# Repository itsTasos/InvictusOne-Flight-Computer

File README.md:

# InvictusOne Flight Computer

A 4-layer flight-data acquisition and logging board for high-power model rockets. The design combines a 3S LiPo power front end, an STM32G474 microcontroller, multiple flight sensors, non-volatile storage, CAN-FD and UART interfaces, and an external watchdog.

The board is intended to measure, timestamp, store, and communicate flight data. It does not include ignition, pyrotechnic, or recovery-deployment circuitry.

## Features

- STM32G474RET6 main controller with 8 MHz high-speed and 32.768 kHz low-speed crystals.
- BMI088 accelerometer and gyroscope, plus an ADXL375 high-g accelerometer with a measurement range up to ±200 g.
- LPS22DF absolute pressure sensor for pressure-based altitude estimation in application firmware.
- 128-Mbit (16-MiB) W25Q128 serial NOR flash for flight-data storage.
- CAN-FD transceiver with line protection and selectable 120 Ω termination.
- 3S battery input protection, electronic fuse, battery-current monitoring, and 3.3 V buck conversion.
- External watchdog connected to the MCU reset line.
- 29 test points on the bottom side.

## Specifications

| Item | Design specification |
|---|---|
| Battery input | 3S LiPo, 9.0–12.6 V nominal operating range |
| Battery protection | TPS25940 eFuse; nominal undervoltage rising/falling thresholds of about 8.67 V / 8.14 V, overvoltage cutoff about 13.53 V |
| Input current limit | About 1.74 A, set by the eFuse current-limit resistor |
| Main logic rail | 3.3 V from a TPS62902 synchronous buck converter |
| Sensor rails | 3V3_SENS and 3V3_BARO are ferrite-filtered branches of 3.3 V, not separate regulated outputs |
| Data storage | 128 Mbit / 16 MiB serial NOR flash |
| Communication | CAN-FD, 3.3 V UART, SWD |
| PCB outline | 50 × 80 mm |
| PCB construction | 4 copper layers, nominal 1.6 mm thickness |
| Mounting | Four 3.2 mm non-plated holes on a 40 × 70 mm pattern |
| Test access | 29 bottom-side test points |

Power thresholds and current limit are nominal resistor-based calculations. They are not per-cell LiPo protection thresholds or measured performance limits.

## Main components

| Reference | Part | Function |
|---|---|---|
| U1 | STM32G474RET6 | Main microcontroller; sensor acquisition, logging control, and communications |
| U2 | TPS3431SQDRBRQ1 | External watchdog; its output can reset the MCU |
| U3 | BMI088 | Accelerometer and gyroscope |
| U4 | ADXL375BCCZ | High-g accelerometer, ±200 g range |
| U5 | LPS22DFTR | Absolute pressure sensor |
| U6 | W25Q128JVSIQ | 128-Mbit serial NOR flash |
| U7 | TCAN3413DR | CAN-FD physical-layer transceiver |
| U8 | TPS25940AQRVCRQ1 | Input eFuse, voltage monitoring, current limiting, and current monitor |
| U9 | TPS62902QRYTRQ1 | Battery-to-3.3 V buck converter |
| U10 | PESD2CANFD24VT-Q | CAN bus transient protection |
| D2 | SMAJ13A-TR | Battery-input TVS diode |
| L1 | XGL4020-102ME, 1 µH | Buck-converter power inductor |

## Power and signal architecture

Battery power enters J1 as VBAT_RAW. The input TVS and eFuse feed VBAT_PROTECTED, which supplies the 3.3 V buck converter and is also available at J2 pin 1. The buck output is 3V3_MAIN. Ferrite filters create the 3V3_SENS branch for the inertial sensors, the 3V3_BARO branch for the pressure sensor, and a filtered VDDA branch for the MCU ADC.

The BMI088 uses SPI1, the ADXL375 uses SPI2, the pressure sensor uses I2C3, and the external flash uses SPI3. The MCU connects to the CAN-FD transceiver through FDCAN1, to J3 through USART2, and to a debug probe through SWD at J4. All board domains share a common ground; the sensor supply branches are filtered but not galvanically isolated.

See [Hardware design](docs/hardware-design.md) for the power path and design calculations, [Connector pinout](docs/pinout.md) for connector and test-point details, and [Programming and debug](docs/programming.md) for the custom SWD connection.

## External connectors

| Connector | Pin | Signal |
|---|---:|---|
| J1 — battery | 1 | VBAT_RAW, battery positive |
|  | 2 | GND |
| J2 — CAN module bus | 1 | VBAT_PROTECTED, battery voltage |
|  | 2 | GND |
|  | 3 | CAN_H |
|  | 4 | CAN_L |
| J3 — UART | 1 | 3V3_MAIN |
|  | 2 | GND |
|  | 3 | UART_TX from MCU |
|  | 4 | UART_RX to MCU |
| J4 — SWD | 1 | 3V3_MAIN / target reference |
|  | 2 | SWDIO |
|  | 3 | GND |
|  | 4 | SWCLK |
|  | 5 | GND |
|  | 6 | NRST |

**J2 pin 1 carries protected battery voltage, not 3.3 V.** J3 is a 3.3 V UART interface, not RS-232. J4 uses a custom six-contact assignment and is not the standard TC2030-CTX pinout. Confirm the pin numbering and cable wiring before connecting external equipment.

## Mechanical orientation

The board is 50 × 80 mm. The +X nose direction is marked on the silkscreen along the long board axis. The pressure-sensor port should remain unobstructed when installed. The four mounting holes are non-plated and form a 40 × 70 mm rectangle.

## Repository layout

- hardware/kicad/ — KiCad project, PCB, hierarchical schematic, design rules, and local symbol and footprint libraries.
- docs/schematic.pdf — rendered hierarchical schematic.
- docs/assets/board-overview.png — PCB layout illustration.
- docs/ — hardware overview, connector pinout, and programming guide.

## Opening the design

Open hardware/kicad/HPR_FC_G474_3S.kicad_pro in KiCad. The PCB, hierarchical schematic, local libraries, and design-rule file are kept together under hardware/kicad/; the project uses paths relative to that directory.

## Design boundaries

The board has no battery charger, cell balancer, individual-cell monitor, or guaranteed reverse-polarity protection. The eFuse monitors the pack input as a whole. Its nominal undervoltage threshold is below the safe minimum for some individual 3S LiPo cells, so it must not be used as cell-level protection.

The CAN interface is not galvanically isolated. The input TVS clamp can exceed the eFuse absolute-maximum input voltage under some surge conditions; validate the power source, wiring, and transient environment for the intended installation. This board is a sensing, logging, and communications platform, not a deployment controller.

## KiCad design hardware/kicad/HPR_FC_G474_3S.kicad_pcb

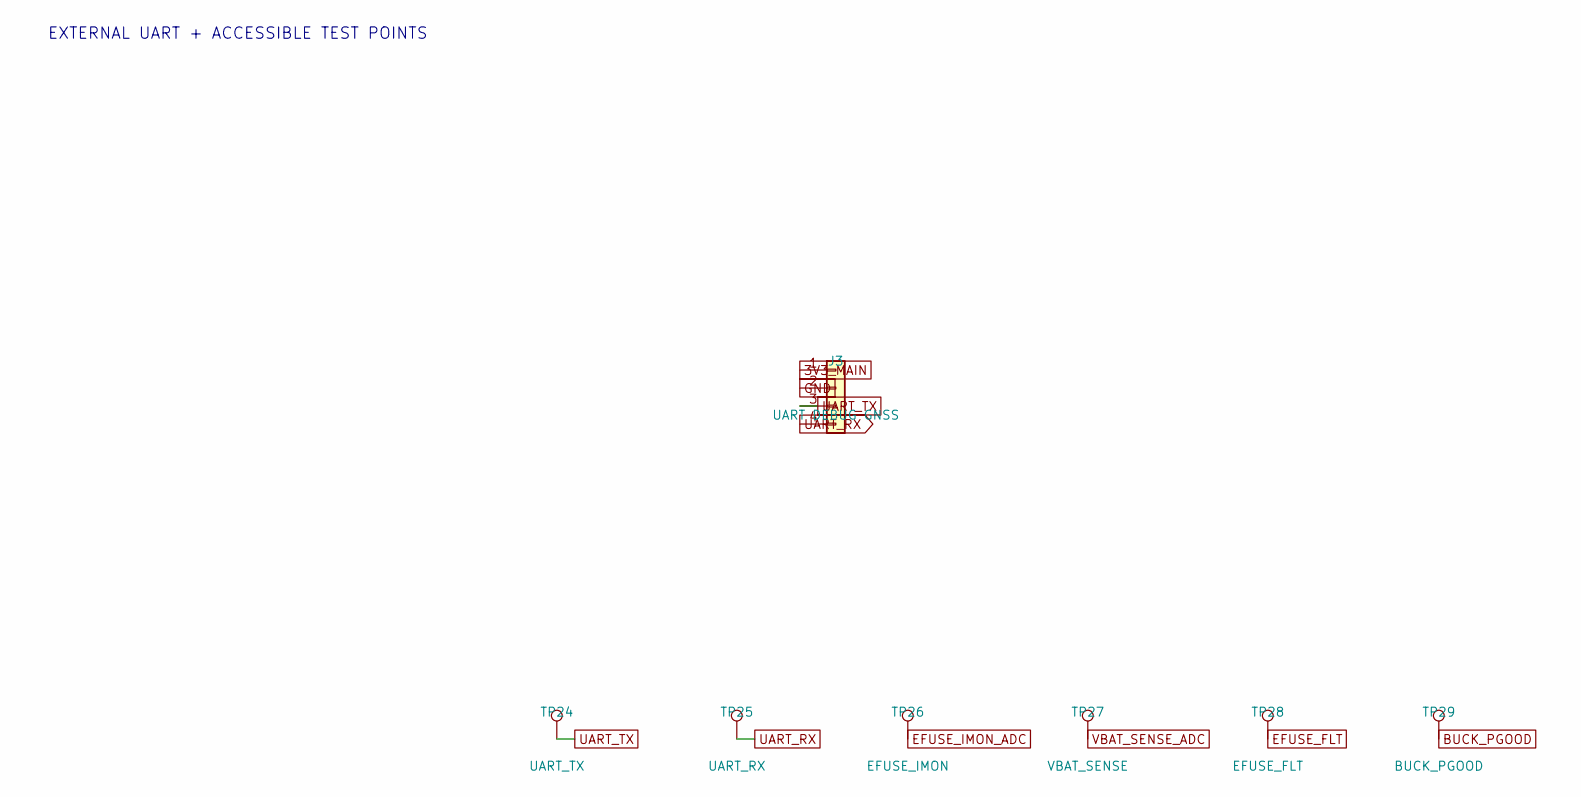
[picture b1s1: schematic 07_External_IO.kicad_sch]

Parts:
J3: UART DEBUG GNSS; JST_GH_SM04B-GHS-TB_1x04-1MP_P1.25mm_Horizontal
TP24: UART_TX; TestPoint_Pad_D1.0mm
TP25: UART_RX; TestPoint_Pad_D1.0mm
TP26: EFUSE_IMON; TestPoint_Pad_D1.0mm
TP27: VBAT_SENSE; TestPoint_Pad_D1.0mm
TP28: EFUSE_FLT; TestPoint_Pad_D1.0mm
TP29: BUCK_PGOOD; TestPoint_Pad_D1.0mm

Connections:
3V3_MAIN: J3.1; also elsewhere on the board
BUCK_PGOOD: TP29.1 (1_1); also elsewhere on the board
EFUSE_FLT: TP28.1 (1_1); also elsewhere on the board
EFUSE_IMON_ADC: TP26.1 (1_1); also elsewhere on the board
GND: J3.2; also elsewhere on the board
UART_RX: J3.4, TP25.1 (1_1); also elsewhere on the board
UART_TX: J3.3, TP24.1 (1_1); also elsewhere on the board
VBAT_SENSE_ADC: TP27.1 (1_1); also elsewhere on the board

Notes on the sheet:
EXTERNAL UART + ACCESSIBLE TEST POINTS

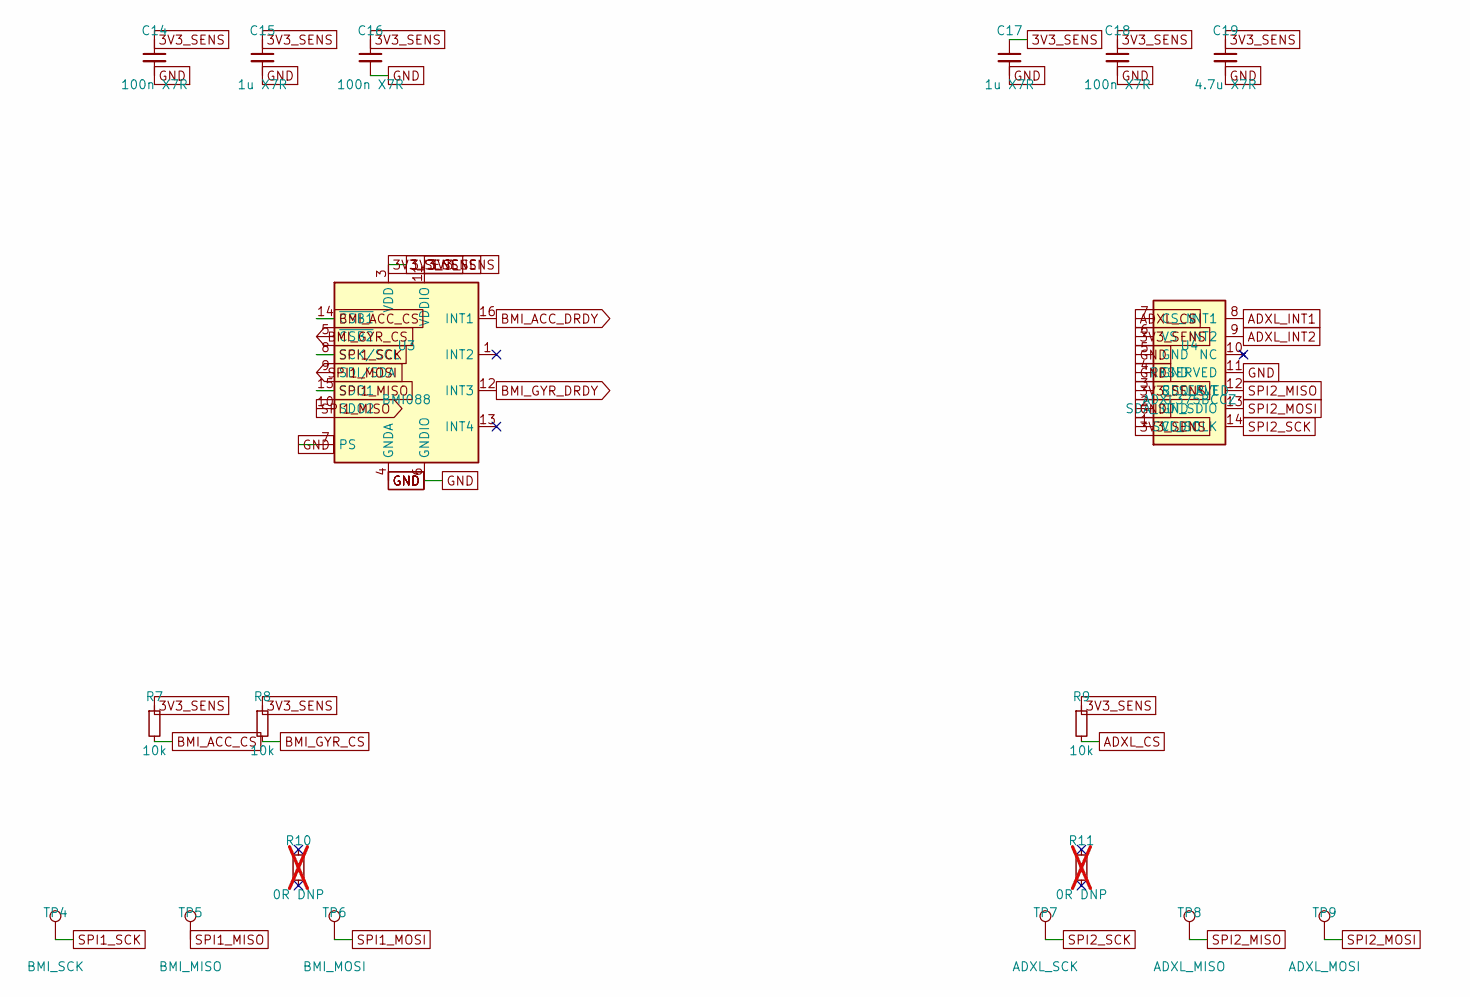
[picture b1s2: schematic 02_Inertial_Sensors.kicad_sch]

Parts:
C14, C16, C18: 100n X7R; C_0402_1005Metric
C15, C17: 1u X7R; C_0603_1608Metric
C19: 4.7u X7R; C_0603_1608Metric
R7, R8, R9: 10k; R_0402_1005Metric
R10, R11: 0R DNP; R_0402_1005Metric; not fitted
TP4: BMI_SCK; TestPoint_Pad_D1.0mm
TP5: BMI_MISO; TestPoint_Pad_D1.0mm
TP6: BMI_MOSI; TestPoint_Pad_D1.0mm
TP7: ADXL_SCK; TestPoint_Pad_D1.0mm
TP8: ADXL_MISO; TestPoint_Pad_D1.0mm
TP9: ADXL_MOSI; TestPoint_Pad_D1.0mm
U3: BMI088; Bosch_LGA-16_4.5x3mm_P0.5mm_LayoutBorder7x1y_ClockwisePinNu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; MPN BMI088
U4: ADXL375BCCZ; Analog_ADXL375_CC-14-1_LGA14_3x5mm_P0.8mm; MPN ADXL375BCCZ

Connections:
3V3_SENS: C14.1, C15.1, C16.1, C17.1, C18.1, C19.1, R7.1, R8.1, R9.1, U3.3 (VDD), U3.11 (VDDIO), U4.1 (VDDIO), U4.3 (RESERVED), U4.6 (VS); also elsewhere on the board
ADXL_CS: R9.2, U4.7 (CS_N); also elsewhere on the board
ADXL_INT1: U4.8 (INT1); also elsewhere on the board
ADXL_INT2: U4.9 (INT2); also elsewhere on the board
BMI_ACC_CS: R7.2, U3.14 (~CSB1); also elsewhere on the board
BMI_ACC_DRDY: U3.16 (INT1); also elsewhere on the board
BMI_GYR_CS: R8.2, U3.5 (~CSB2); also elsewhere on the board
BMI_GYR_DRDY: U3.12 (INT3); also elsewhere on the board
GND: C14.2, C15.2, C16.2, C17.2, C18.2, C19.2, U3.2 (GNDA), U3.4 (GNDA), U3.6 (GNDIO), U3.7 (PS), U4.2 (GND), U4.4 (GND), U4.5 (GND), U4.11 (RESERVED); also elsewhere on the board
SPI1_MISO: TP5.1 (1_1), U3.10 (SDO2), U3.15 (SDO1); also elsewhere on the board
SPI1_MOSI: TP6.1 (1_1), U3.9 (SDI/SDA); also elsewhere on the board
SPI1_SCK: TP4.1 (1_1), U3.8 (SCK/SCL); also elsewhere on the board
SPI2_MISO: TP8.1 (1_1), U4.12 (SDO_ALT); also elsewhere on the board
SPI2_MOSI: TP9.1 (1_1), U4.13 (SDA_SDI_SDIO); also elsewhere on the board
SPI2_SCK: TP7.1 (1_1), U4.14 (SCL_SCLK); also elsewhere on the board

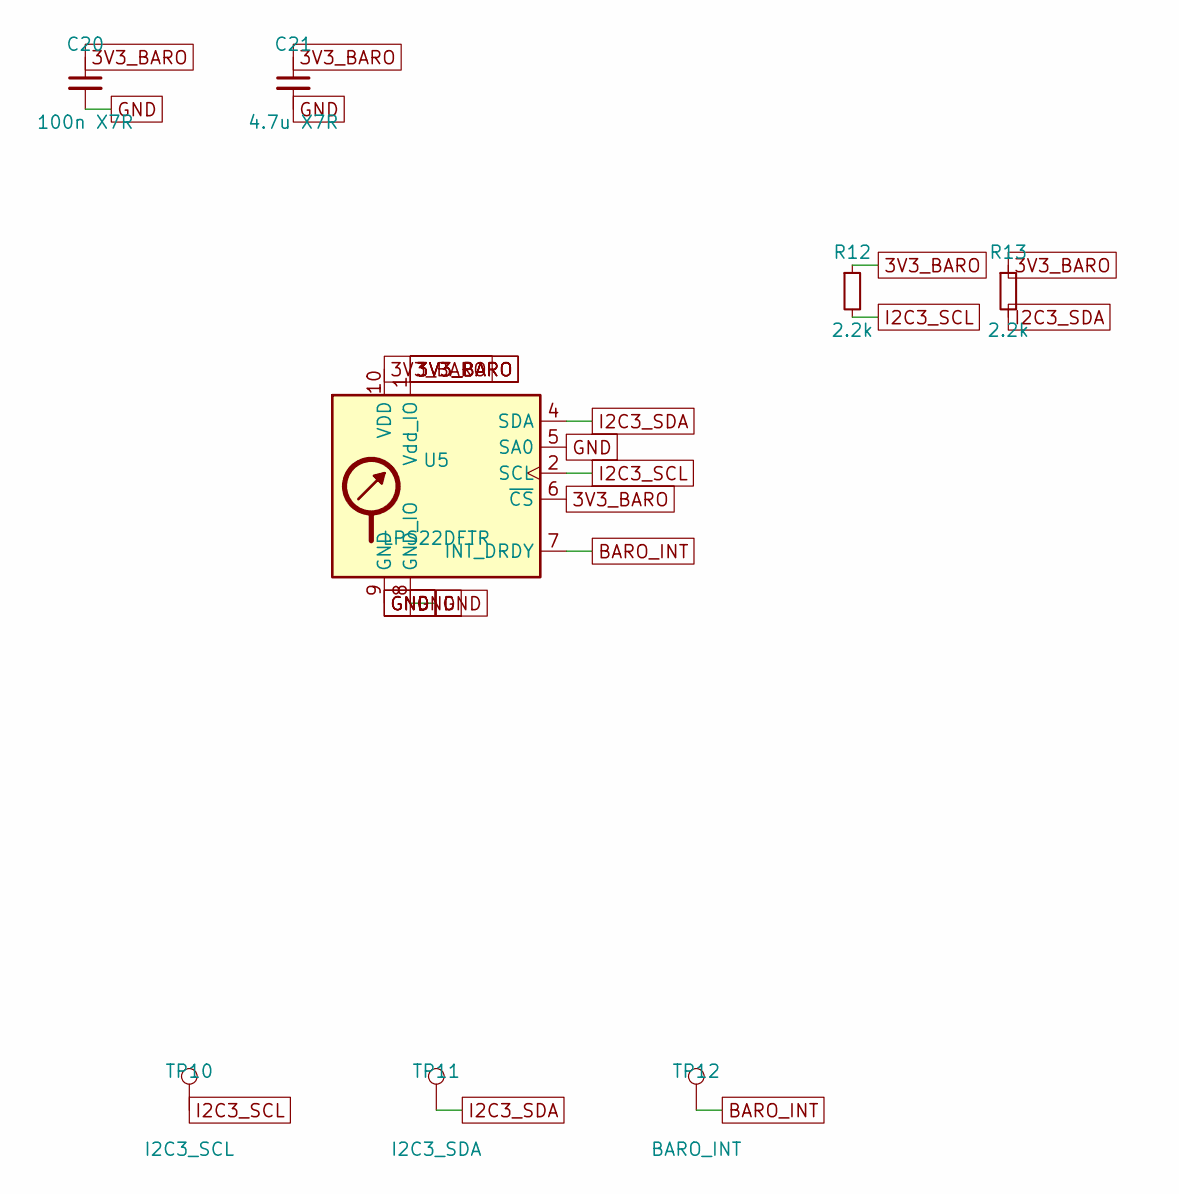
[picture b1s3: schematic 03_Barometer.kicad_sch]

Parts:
C20: 100n X7R; C_0402_1005Metric
C21: 4.7u X7R; C_0603_1608Metric
R12, R13: 2.2k; R_0402_1005Metric
TP10: I2C3_SCL; TestPoint_Pad_D1.0mm
TP11: I2C3_SDA; TestPoint_Pad_D1.0mm
TP12: BARO_INT; TestPoint_Pad_D1.0mm
U5: LPS22DFTR; ST_HLGA-10_2x2mm_P0.5mm_LayoutBorder3x2y; MPN LPS22DFTR

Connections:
3V3_BARO: C20.1, C21.1, R12.1, R13.1, U5.1 (Vdd_IO), U5.6 (~CS), U5.10 (VDD); also elsewhere on the board
BARO_INT: TP12.1 (1_1), U5.7 (INT_DRDY); also elsewhere on the board
GND: C20.2, C21.2, U5.3 (GND), U5.5 (SA0), U5.8 (GND_IO), U5.9 (GND); also elsewhere on the board
I2C3_SCL: R12.2, TP10.1 (1_1), U5.2 (SCL); also elsewhere on the board
I2C3_SDA: R13.2, TP11.1 (1_1), U5.4 (SDA); also elsewhere on the board

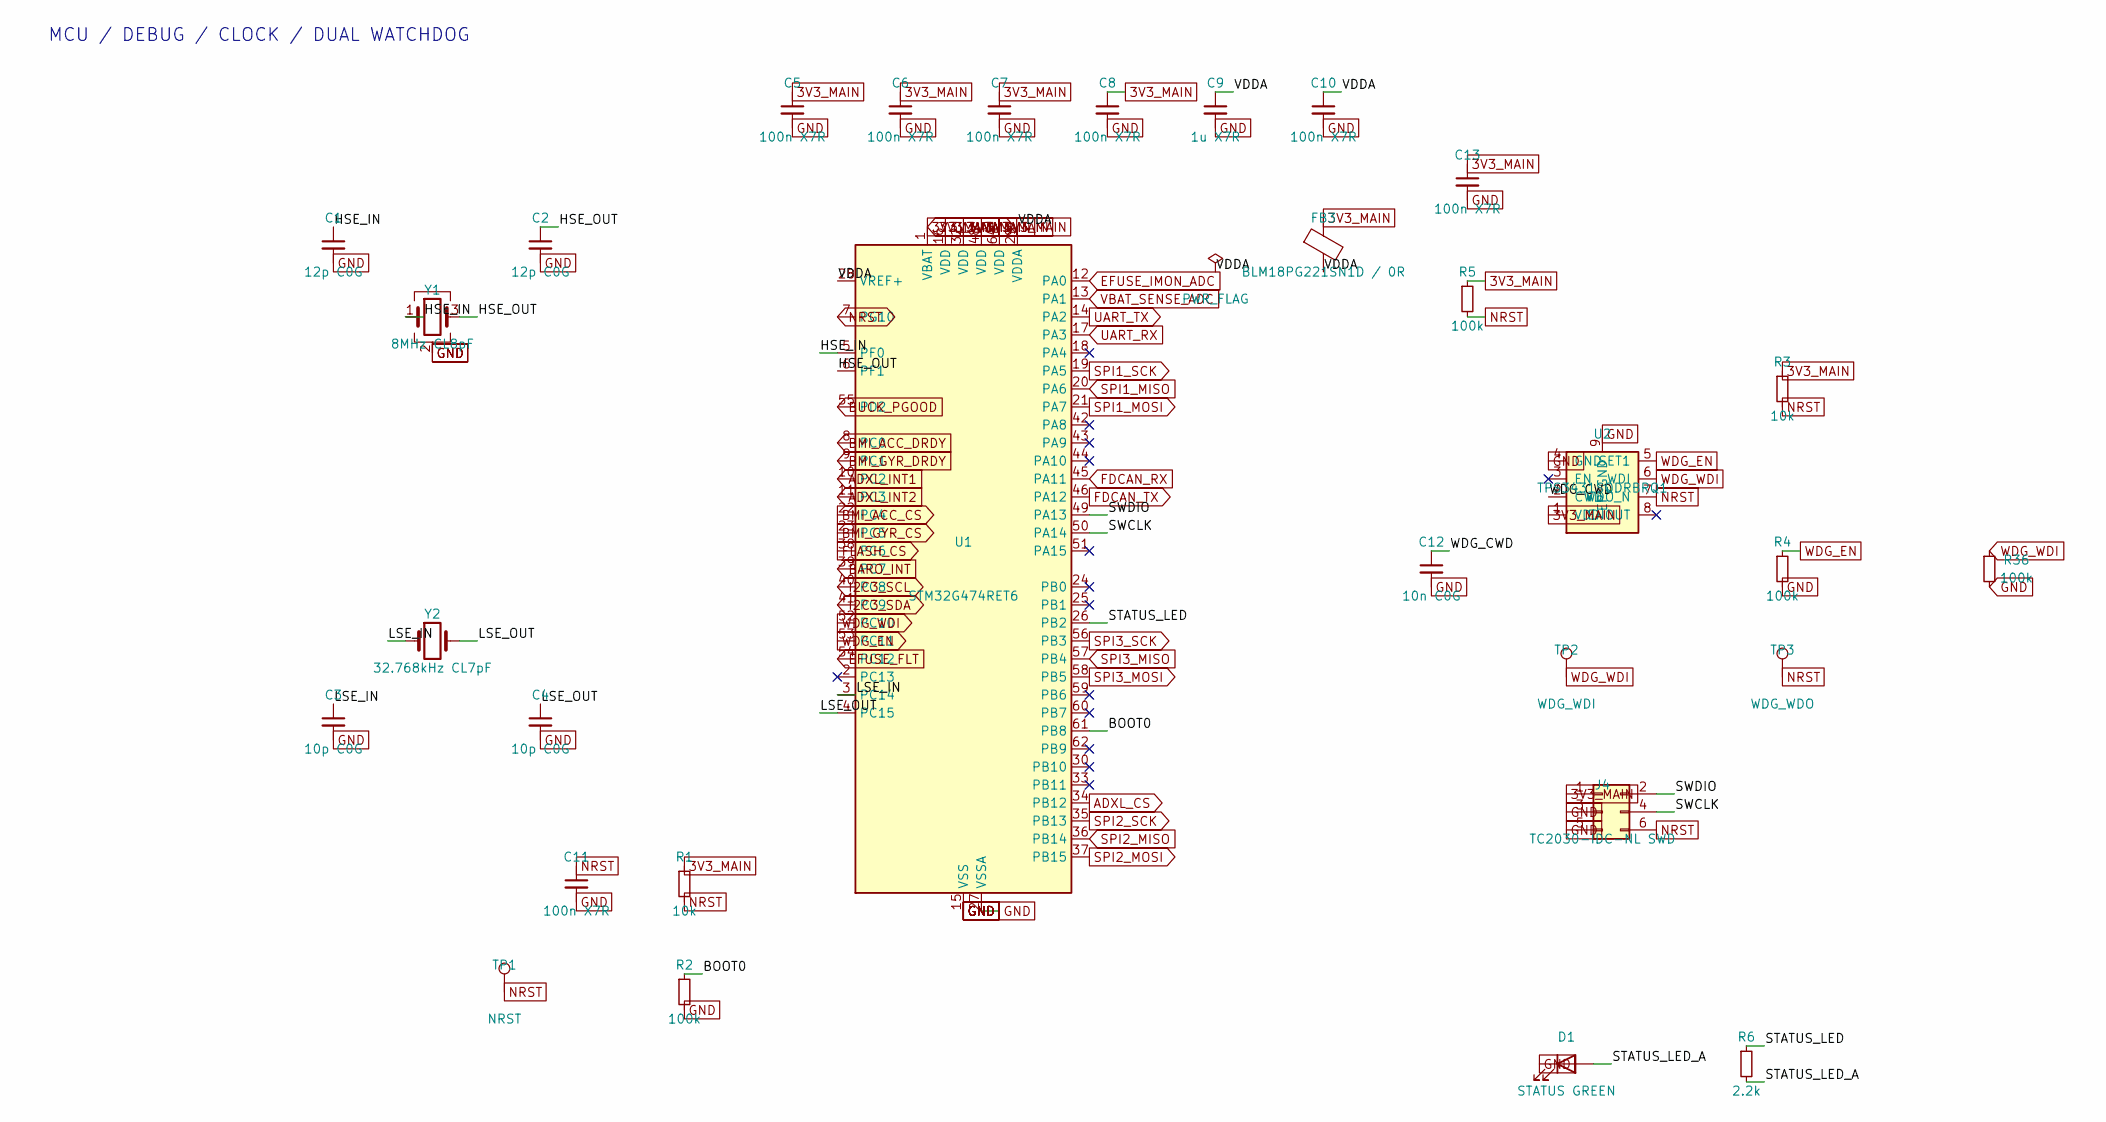
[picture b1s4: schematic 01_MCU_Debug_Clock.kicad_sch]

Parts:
C1, C2: 12p C0G; C_0402_1005Metric
C3, C4: 10p C0G; C_0402_1005Metric
C5, C6, C7, C8, C10, C11, C13: 100n X7R; C_0402_1005Metric
C9: 1u X7R; C_0603_1608Metric
C12: 10n C0G; C_0402_1005Metric
D1: STATUS GREEN; LED_0603_1608Metric
FB3: BLM18PG221SN1D / 0R; L_0603_1608Metric_Pad1.05x0.95mm_HandSolder; MPN BLM18PG221SN1D
J4: TC2030-IDC-NL SWD; TagConnect_TC2030-IDC-NL
R1, R3: 10k; R_0402_1005Metric
R2, R4, R5, R36: 100k; R_0402_1005Metric
R6: 2.2k; R_0402_1005Metric
TP1: NRST; TestPoint_Pad_D1.0mm
TP2: WDG_WDI; TestPoint_Pad_D1.0mm
TP3: WDG_WDO; TestPoint_Pad_D1.0mm
U1: STM32G474RET6; LQFP-64_10x10mm_P0.5mm; MPN STM32G474RET6
U2: TPS3431SQDRBRQ1; HPR_U2_verified_geometry; MPN TPS3431SQDRBRQ1
Y1: 8MHz CL8pF; Crystal_SMD_3225-4Pin_3.2x2.5mm; MPN ECS-80-8-33-JGN-TR3
Y2: 32.768kHz CL7pF; Crystal_SMD_3215-2Pin_3.2x1.5mm; MPN ABS07-32.768KHZ-7-T

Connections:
3V3_MAIN: C5.1, C6.1, C7.1, C8.1, C13.1, FB3.1, J4.1, R1.1, R3.1, R5.1, U1.1 (VBAT), U1.16 (VDD), U1.32 (VDD), U1.48 (VDD), U1.64 (VDD), U2.1 (VDD); also elsewhere on the board
/MFC_G474 SYSTEM/MCU / DEBUG / CLOCK/BOOT0: R2.1, U1.61 (PB8)
/MFC_G474 SYSTEM/MCU / DEBUG / CLOCK/HSE_IN: C1.1, U1.5 (PF0), Y1.1
/MFC_G474 SYSTEM/MCU / DEBUG / CLOCK/HSE_OUT: C2.1, U1.6 (PF1), Y1.3
/MFC_G474 SYSTEM/MCU / DEBUG / CLOCK/LSE_IN: C3.1, U1.3 (PC14), Y2.1
/MFC_G474 SYSTEM/MCU / DEBUG / CLOCK/LSE_OUT: C4.1, U1.4 (PC15), Y2.2
/MFC_G474 SYSTEM/MCU / DEBUG / CLOCK/STATUS_LED: R6.1, U1.26 (PB2)
/MFC_G474 SYSTEM/MCU / DEBUG / CLOCK/STATUS_LED_A: D1.2 (A), R6.2
/MFC_G474 SYSTEM/MCU / DEBUG / CLOCK/SWCLK: J4.4, U1.50 (PA14)
/MFC_G474 SYSTEM/MCU / DEBUG / CLOCK/SWDIO: J4.2, U1.49 (PA13)
/MFC_G474 SYSTEM/MCU / DEBUG / CLOCK/VDDA: C9.1, C10.1, FB3.2, U1.28 (VREF+), U1.29 (VDDA)
/MFC_G474 SYSTEM/MCU / DEBUG / CLOCK/WDG_CWD: C12.1, U2.2 (CWD)
ADXL_CS: U1.34 (PB12); also elsewhere on the board
ADXL_INT1: U1.10 (PC2); also elsewhere on the board
ADXL_INT2: U1.11 (PC3); also elsewhere on the board
BARO_INT: U1.39 (PC7); also elsewhere on the board
BMI_ACC_CS: U1.22 (PC4); also elsewhere on the board
BMI_ACC_DRDY: U1.8 (PC0); also elsewhere on the board
BMI_GYR_CS: U1.23 (PC5); also elsewhere on the board
BMI_GYR_DRDY: U1.9 (PC1); also elsewhere on the board
BUCK_PGOOD: U1.55 (PD2); also elsewhere on the board
EFUSE_FLT: U1.54 (PC12); also elsewhere on the board
EFUSE_IMON_ADC: U1.12 (PA0); also elsewhere on the board
FDCAN_RX: U1.45 (PA11); also elsewhere on the board
FDCAN_TX: U1.46 (PA12); also elsewhere on the board
FLASH_CS: U1.38 (PC6); also elsewhere on the board
GND: C1.2, C2.2, C3.2, C4.2, C5.2, C6.2, C7.2, C8.2, C9.2, C10.2, C11.2, C12.2, C13.2, D1.1 (K), J4.3, J4.5, R2.2, R4.2, R36.2, U1.15 (VSS), U1.27 (VSSA), U1.31 (VSS), U1.47 (VSS), U1.63 (VSS), U2.4 (GND), U2.9 (EP_GND), Y1.2 (G), Y1.4 (G); also elsewhere on the board
I2C3_SCL: U1.40 (PC8); also elsewhere on the board
I2C3_SDA: U1.41 (PC9); also elsewhere on the board
NRST: C11.1, J4.6, R1.2, R3.2, R5.2, TP1.1 (1_1), TP3.1 (1_1), U1.7 (PG10), U2.7 (WDO_N)
SPI1_MISO: U1.20 (PA6); also elsewhere on the board
SPI1_MOSI: U1.21 (PA7); also elsewhere on the board
SPI1_SCK: U1.19 (PA5); also elsewhere on the board
SPI2_MISO: U1.36 (PB14); also elsewhere on the board
SPI2_MOSI: U1.37 (PB15); also elsewhere on the board
SPI2_SCK: U1.35 (PB13); also elsewhere on the board
SPI3_MISO: U1.57 (PB4); also elsewhere on the board
SPI3_MOSI: U1.58 (PB5); also elsewhere on the board
SPI3_SCK: U1.56 (PB3); also elsewhere on the board
UART_RX: U1.17 (PA3); also elsewhere on the board
UART_TX: U1.14 (PA2); also elsewhere on the board
VBAT_SENSE_ADC: U1.13 (PA1); also elsewhere on the board
WDG_EN: R4.1, U1.53 (PC11), U2.5 (SET1)
WDG_WDI: R36.1, TP2.1 (1_1), U1.52 (PC10), U2.6 (WDI)

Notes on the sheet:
MCU / DEBUG / CLOCK / DUAL WATCHDOG

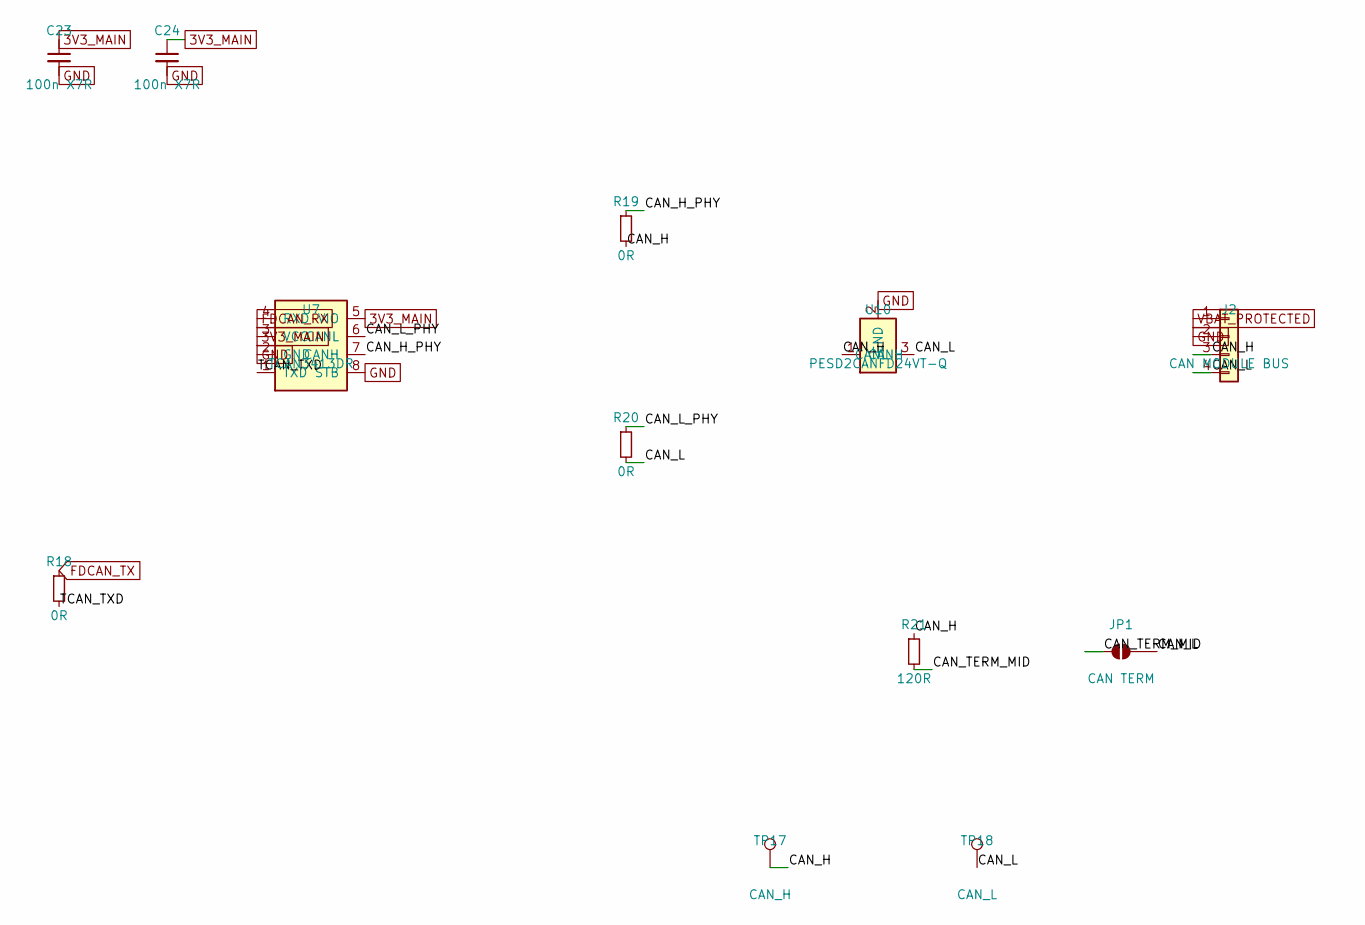
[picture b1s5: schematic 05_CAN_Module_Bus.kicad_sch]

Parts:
C23, C24: 100n X7R; C_0402_1005Metric
J2: CAN MODULE BUS; JST_GH_SM04B-GHS-TB_1x04-1MP_P1.25mm_Horizontal
JP1: CAN TERM; SolderJumper-2_P1.3mm_Open_Pad1.0x1.5mm
R18: 0R; R_0402_1005Metric
R19, R20: 0R; R_0603_1608Metric
R21: 120R; R_0603_1608Metric
TP17: CAN_H; TestPoint_Pad_D1.0mm
TP18: CAN_L; TestPoint_Pad_D1.0mm
U7: TCAN3413DR; SOIC-8_3.9x4.9mm_P1.27mm; MPN TCAN3413DR
U10: PESD2CANFD24VT-Q; SOT-23; MPN PESD2CANFD24VT-Q

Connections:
3V3_MAIN: C23.1, C24.1, U7.3 (VCC), U7.5 (VIO); also elsewhere on the board
/MFC_G474 SYSTEM/CAN-FD MODULE BUS/CAN_H: J2.3, R19.2, R21.1, TP17.1 (1_1), U10.1 (CANH)
/MFC_G474 SYSTEM/CAN-FD MODULE BUS/CAN_H_PHY: R19.1, U7.7 (CANH)
/MFC_G474 SYSTEM/CAN-FD MODULE BUS/CAN_L: J2.4, JP1.2 (B), R20.2, TP18.1 (1_1), U10.3 (CANL)
/MFC_G474 SYSTEM/CAN-FD MODULE BUS/CAN_L_PHY: R20.1, U7.6 (CANL)
/MFC_G474 SYSTEM/CAN-FD MODULE BUS/CAN_TERM_MID: JP1.1 (A), R21.2
/MFC_G474 SYSTEM/CAN-FD MODULE BUS/TCAN_TXD: R18.2, U7.1 (TXD)
FDCAN_RX: U7.4 (RXD); also elsewhere on the board
FDCAN_TX: R18.1; also elsewhere on the board
GND: C23.2, C24.2, J2.2, U7.2 (GND), U7.8 (STB), U10.2 (GND); also elsewhere on the board
VBAT_PROTECTED: J2.1; also elsewhere on the board

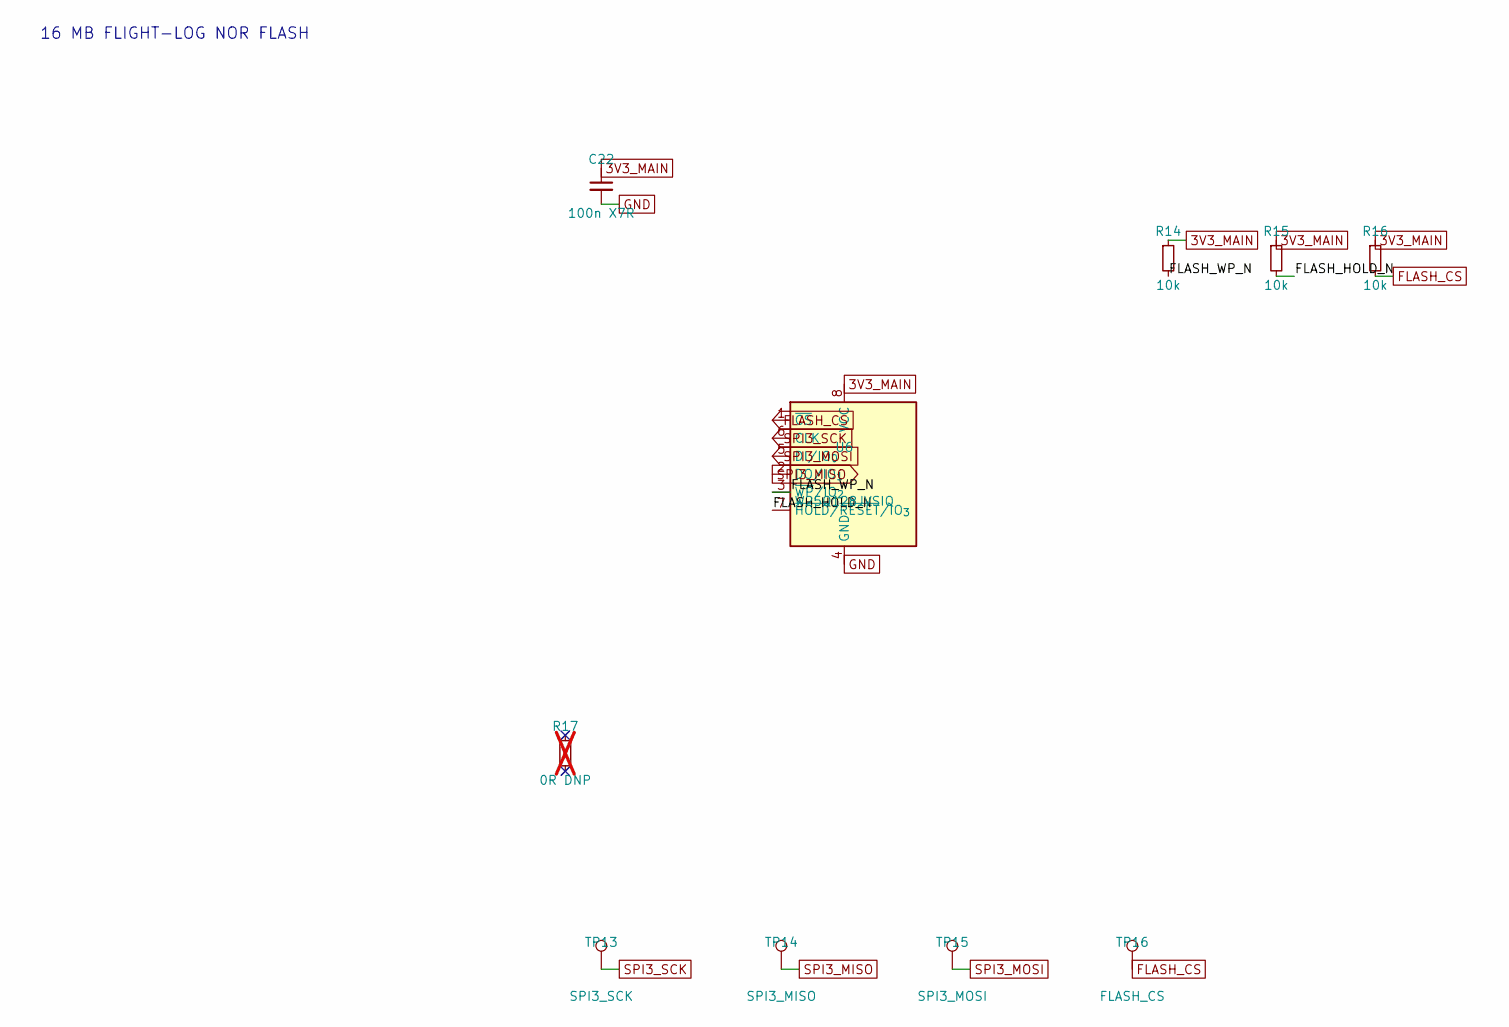
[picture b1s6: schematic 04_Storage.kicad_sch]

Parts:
C22: 100n X7R; C_0402_1005Metric
R14, R15, R16: 10k; R_0402_1005Metric
R17: 0R DNP; R_0402_1005Metric; not fitted
TP13: SPI3_SCK; TestPoint_Pad_D1.0mm
TP14: SPI3_MISO; TestPoint_Pad_D1.0mm
TP15: SPI3_MOSI; TestPoint_Pad_D1.0mm
TP16: FLASH_CS; TestPoint_Pad_D1.0mm
U6: W25Q128JVSIQ; SOIC-8_5.3x5.3mm_P1.27mm; MPN W25Q128JVSIQ

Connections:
3V3_MAIN: C22.1, R14.1, R15.1, R16.1, U6.8 (VCC); also elsewhere on the board
/MFC_G474 SYSTEM/FLIGHT-LOG STORAGE/FLASH_HOLD_N: R15.2, U6.7 (~HOLD/~RESET/IO_{3})
/MFC_G474 SYSTEM/FLIGHT-LOG STORAGE/FLASH_WP_N: R14.2, U6.3 (~WP/IO_{2})
FLASH_CS: R16.2, TP16.1 (1_1), U6.1 (~CS); also elsewhere on the board
GND: C22.2, U6.4 (GND); also elsewhere on the board
SPI3_MISO: TP14.1 (1_1), U6.2 (DO/IO_{1}); also elsewhere on the board
SPI3_MOSI: TP15.1 (1_1), U6.5 (DI/IO_{0}); also elsewhere on the board
SPI3_SCK: TP13.1 (1_1), U6.6 (CLK); also elsewhere on the board

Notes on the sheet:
16 MB FLIGHT-LOG NOR FLASH

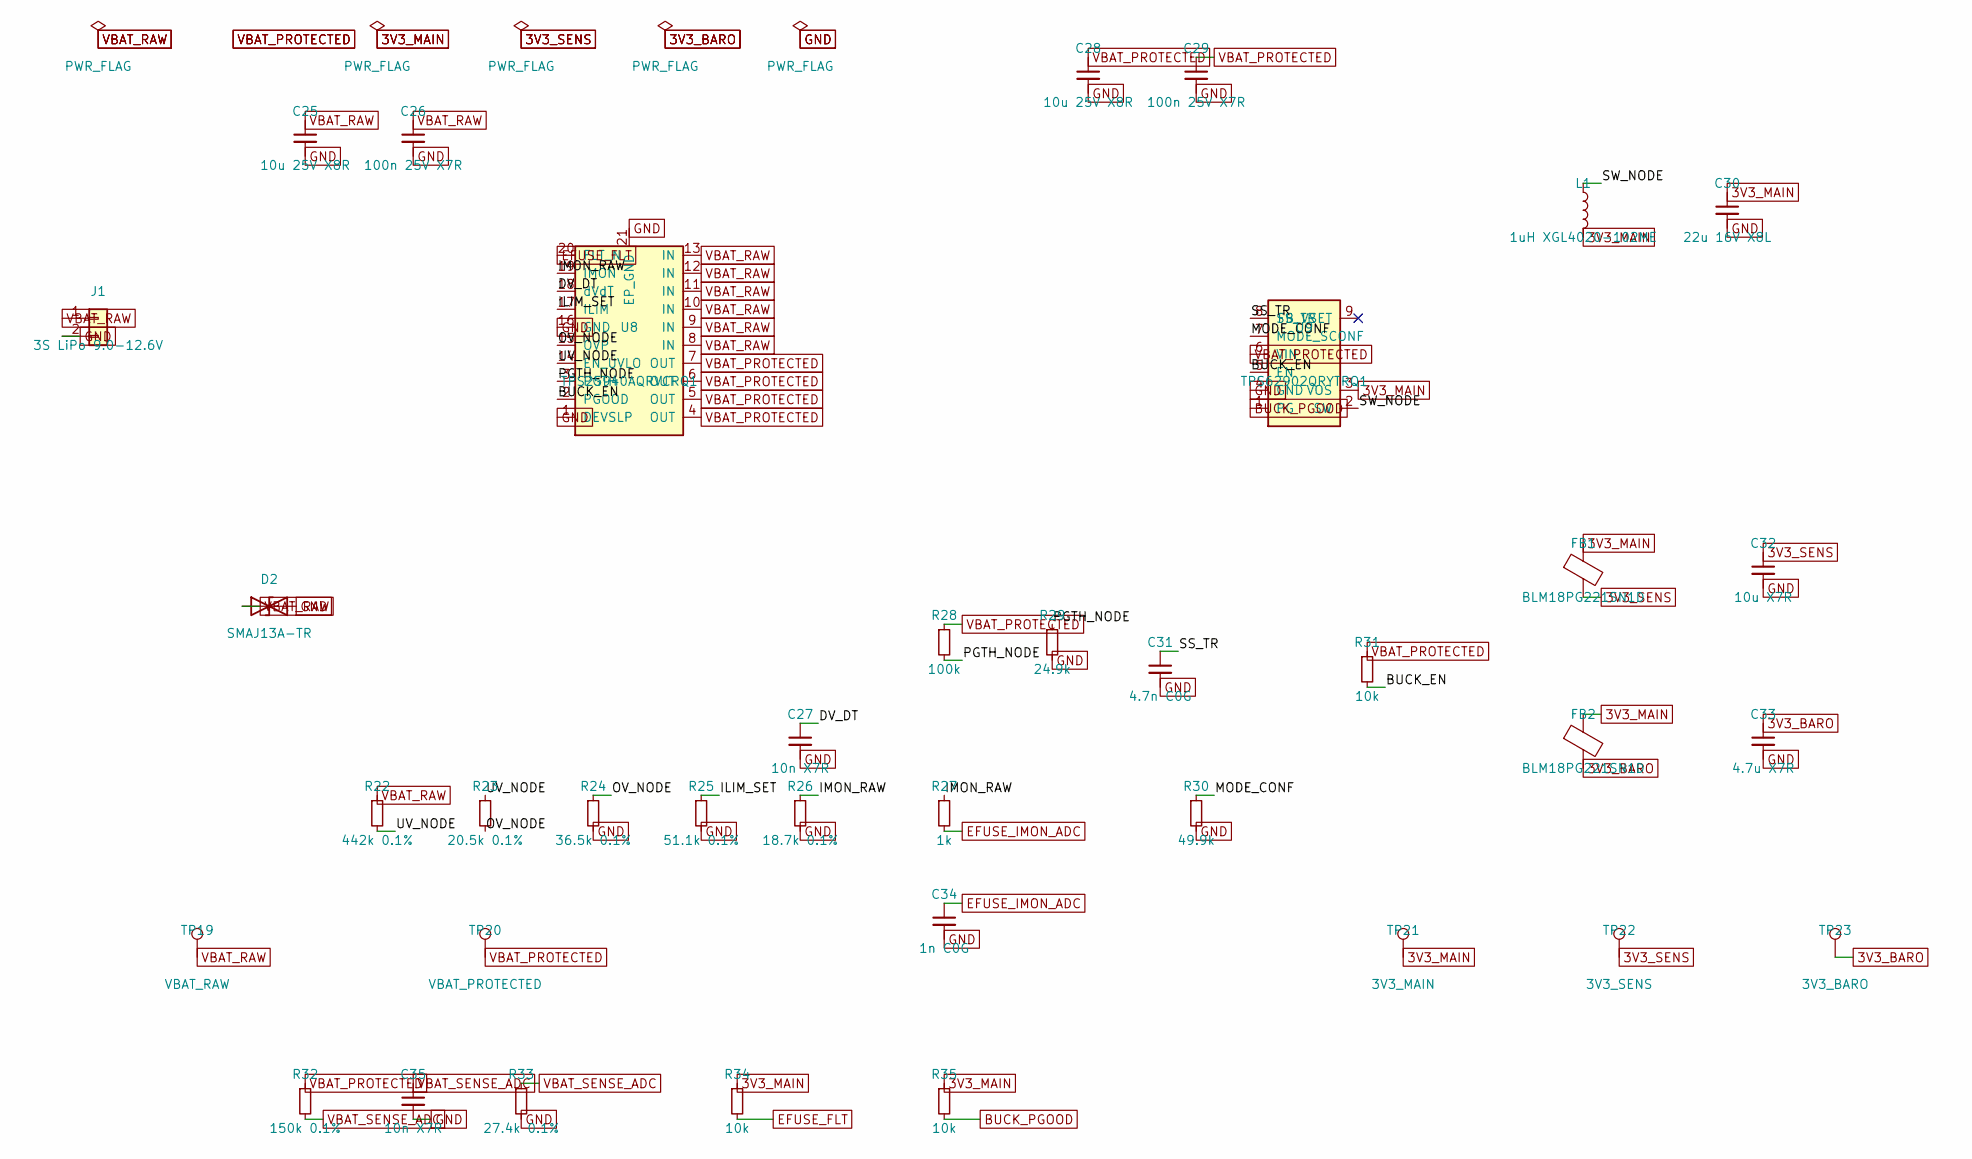
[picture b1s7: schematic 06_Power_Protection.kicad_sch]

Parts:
C25, C28: 10u 25V X8R; C_1210_3225Metric
C26, C29: 100n 25V X7R; C_0603_1608Metric
C27, C35: 10n X7R; C_0402_1005Metric
C30: 22u 16V X8L; C_1210_3225Metric
C31: 4.7n C0G; C_0402_1005Metric
C32: 10u X7R; C_0805_2012Metric
C33: 4.7u X7R; C_0603_1608Metric
C34: 1n C0G; C_0402_1005Metric
D2: SMAJ13A-TR; D_SMA; MPN SMAJ13A-TR
FB1, FB2: BLM18PG221SN1D; L_0603_1608Metric_Pad1.05x0.95mm_HandSolder; MPN BLM18PG221SN1D
J1: 3S LiPo 9.0-12.6V; HPR_MicroFit_2P_Edge
L1: 1uH XGL4020-102ME; L_Coilcraft_XxL4020; MPN XGL4020-102ME
R22: 442k 0.1%; R_0402_1005Metric
R23: 20.5k 0.1%; R_0402_1005Metric
R24: 36.5k 0.1%; R_0402_1005Metric
R25: 51.1k 0.1%; R_0402_1005Metric
R26: 18.7k 0.1%; R_0402_1005Metric
R27: 1k; R_0402_1005Metric
R28: 100k; R_0402_1005Metric
R29: 24.9k; R_0402_1005Metric
R30: 49.9k; R_0402_1005Metric
R31, R34, R35: 10k; R_0402_1005Metric
R32: 150k 0.1%; R_0402_1005Metric
R33: 27.4k 0.1%; R_0402_1005Metric
TP19: VBAT_RAW; TestPoint_Pad_D1.5mm
TP20: VBAT_PROTECTED; TestPoint_Pad_D1.5mm
TP21: 3V3_MAIN; TestPoint_Pad_D1.5mm
TP22: 3V3_SENS; TestPoint_Pad_D1.0mm
TP23: 3V3_BARO; TestPoint_Pad_D1.0mm
U8: TPS25940AQRVCRQ1; HPR_U8_verified_geometry; MPN TPS25940AQRVCRQ1
U9: TPS62902QRYTRQ1; Texas_RYT0009A_VQFN-HR-9_2.2x2.0mm_P0.5mm; MPN TPS62902QRYTRQ1

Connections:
3V3_BARO: C33.1, FB2.2, TP23.1 (1_1); also elsewhere on the board
3V3_MAIN: C30.1, FB1.1, FB2.1, L1.2, R34.1, R35.1, TP21.1 (1_1), U9.3 (VOS); also elsewhere on the board
3V3_SENS: C32.1, FB1.2, TP22.1 (1_1); also elsewhere on the board
/MFC_G474 SYSTEM/POWER / PROTECTION/BUCK_EN: R31.2, U8.2 (PGOOD), U9.5 (EN)
/MFC_G474 SYSTEM/POWER / PROTECTION/DV_DT: C27.1, U8.18 (dVdT)
/MFC_G474 SYSTEM/POWER / PROTECTION/ILIM_SET: R25.1, U8.17 (ILIM)
/MFC_G474 SYSTEM/POWER / PROTECTION/IMON_RAW: R26.1, R27.1, U8.19 (IMON)
/MFC_G474 SYSTEM/POWER / PROTECTION/MODE_CONF: R30.1, U9.7 (MODE_SCONF)
/MFC_G474 SYSTEM/POWER / PROTECTION/OV_NODE: R23.2, R24.1, U8.15 (OVP)
/MFC_G474 SYSTEM/POWER / PROTECTION/PGTH_NODE: R28.2, R29.1, U8.3 (PGTH)
/MFC_G474 SYSTEM/POWER / PROTECTION/SS_TR: C31.1, U9.8 (SS_TR)
/MFC_G474 SYSTEM/POWER / PROTECTION/SW_NODE: L1.1, U9.2 (SW)
/MFC_G474 SYSTEM/POWER / PROTECTION/UV_NODE: R22.2, R23.1, U8.14 (EN_UVLO)
BUCK_PGOOD: R35.2, U9.1 (PG); also elsewhere on the board
EFUSE_FLT: R34.2, U8.20 (FLT_N); also elsewhere on the board
EFUSE_IMON_ADC: C34.1, R27.2; also elsewhere on the board
GND: C25.2, C26.2, C27.2, C28.2, C29.2, C30.2, C31.2, C32.2, C33.2, C34.2, C35.2, D2.2 (A2), J1.2, R24.2, R25.2, R26.2, R29.2, R30.2, R33.2, U8.1 (DEVSLP), U8.16 (GND), U8.21 (EP_GND), U9.4 (GND); also elsewhere on the board
VBAT_PROTECTED: C28.1, C29.1, R28.1, R31.1, R32.1, TP20.1 (1_1), U8.4 (OUT), U8.5 (OUT), U8.6 (OUT), U8.7 (OUT), U9.6 (VIN); also elsewhere on the board
VBAT_RAW: C25.1, C26.1, D2.1 (A1), J1.1, R22.1, TP19.1 (1_1), U8.8 (IN), U8.9 (IN), U8.10 (IN), U8.11 (IN), U8.12 (IN), U8.13 (IN)
VBAT_SENSE_ADC: C35.1, R32.2, R33.1; also elsewhere on the board
